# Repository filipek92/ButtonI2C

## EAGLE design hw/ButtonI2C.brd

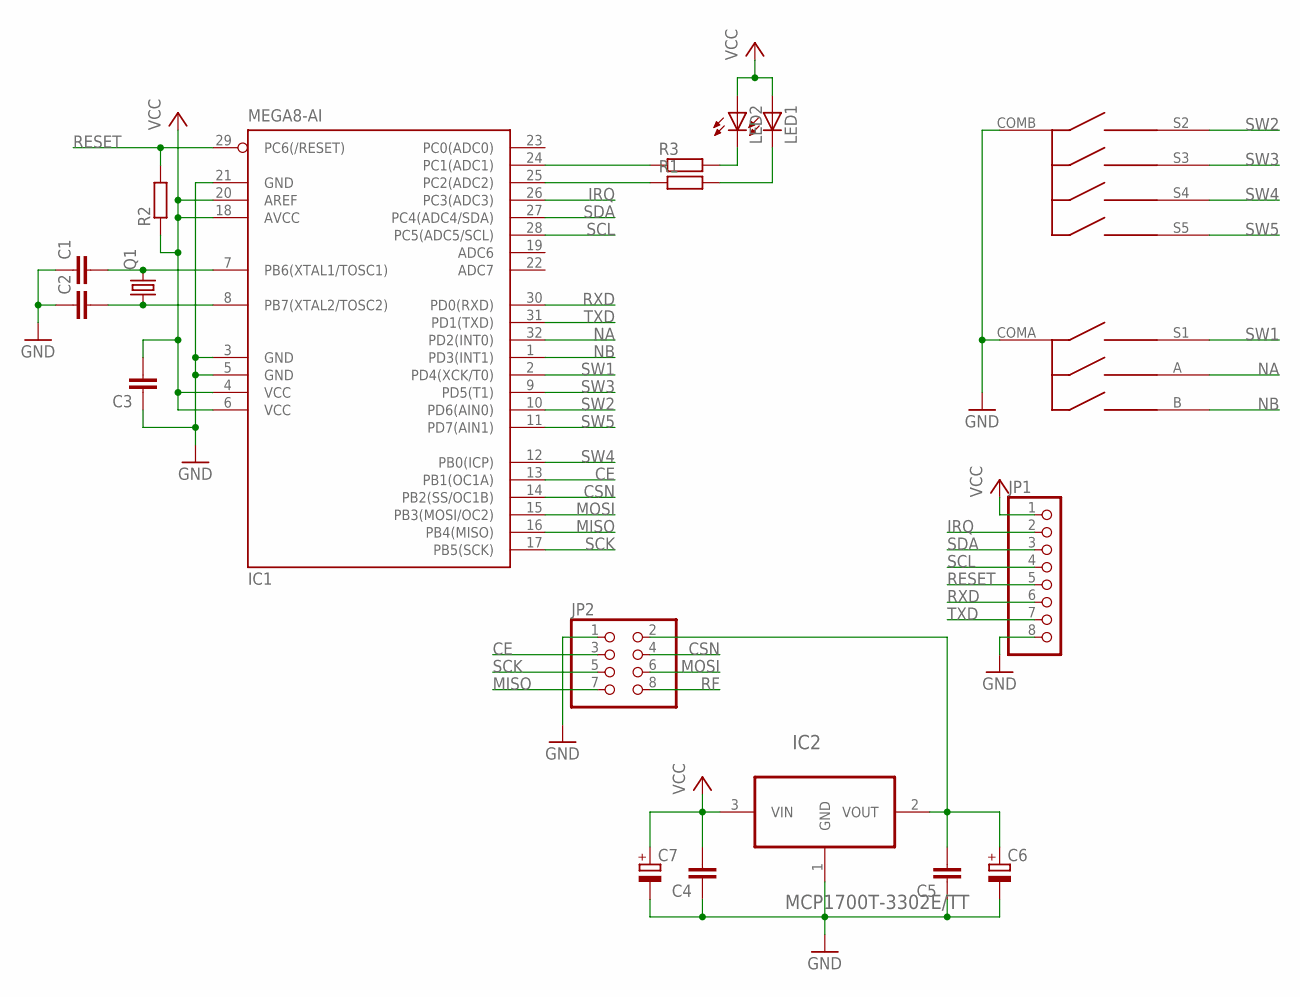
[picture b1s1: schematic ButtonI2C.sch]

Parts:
C1, C2, C3, C4, C5: C-EUC0805K; C0805K
C6, C7: CPOL-EUE2.5-6; E2,5-6
IC1: MEGA8-AI; TQFP32-08
IC2: MCP1700T-3302E/TT; SOT95P237X112-3N
JP1: PINHD-1X8; 1X08
JP2: PINHD-2X4; 2X04
LED1, LED2: LEDCHIPLED_0805; CHIPLED_0805
Q1: CRYSTALHC49UP; HC49UP
R1, R2, R3: R-EU_M0805; M0805
U$1: ANO-I1B-M1B-O2B-S-Z

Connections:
CE: IC1.13 (PB1(OC1A)), JP2.3
CSN: IC1.14 (PB2(SS/OC1B)), JP2.4
GND: C1.1, C2.1, C3.1, C4.1, C5.1, C6.-, C7.-, IC1.3 (GND), IC1.5 (GND), IC1.21 (GND), IC2.1 (GND), JP1.8, JP2.1, U$1.COMA, U$1.COMB
IRQ: IC1.26 (PC3(ADC3)), JP1.2
MISO: IC1.16 (PB4(MISO)), JP2.7
MOSI: IC1.15 (PB3(MOSI/OC2)), JP2.6
unnamed: C2.2, IC1.8 (PB7(XTAL2/TOSC2)), Q1.1
unnamed: C1.2, IC1.7 (PB6(XTAL1/TOSC1)), Q1.2
unnamed: IC1.25 (PC2(ADC2)), R1.1
unnamed: LED1.C, R1.2
unnamed: LED2.C, R3.2
unnamed: IC1.24 (PC1(ADC1)), R3.1
unnamed: C5.2, C6.+, IC2.2 (VOUT), JP2.2
NA: IC1.32 (PD2(INT0)), U$1.A
NB: IC1.1 (PD3(INT1)), U$1.B
RESET: IC1.29 (PC6(/RESET)), JP1.5, R2.2
RF: JP2.8
RXD: IC1.30 (PD0(RXD)), JP1.6
SCK: IC1.17 (PB5(SCK)), JP2.5
SCL: IC1.28 (PC5(ADC5/SCL)), JP1.4
SDA: IC1.27 (PC4(ADC4/SDA)), JP1.3
SW1: IC1.2 (PD4(XCK/T0)), U$1.S1
SW2: IC1.10 (PD6(AIN0)), U$1.S2
SW3: IC1.9 (PD5(T1)), U$1.S3
SW4: IC1.12 (PB0(ICP)), U$1.S4
SW5: IC1.11 (PD7(AIN1)), U$1.S5
TXD: IC1.31 (PD1(TXD)), JP1.7
VCC: C3.2, C4.2, C7.+, IC1.4 (VCC), IC1.6 (VCC), IC1.18 (AVCC), IC1.20 (AREF), IC2.3 (VIN), JP1.1, LED1.A, LED2.A, R2.1

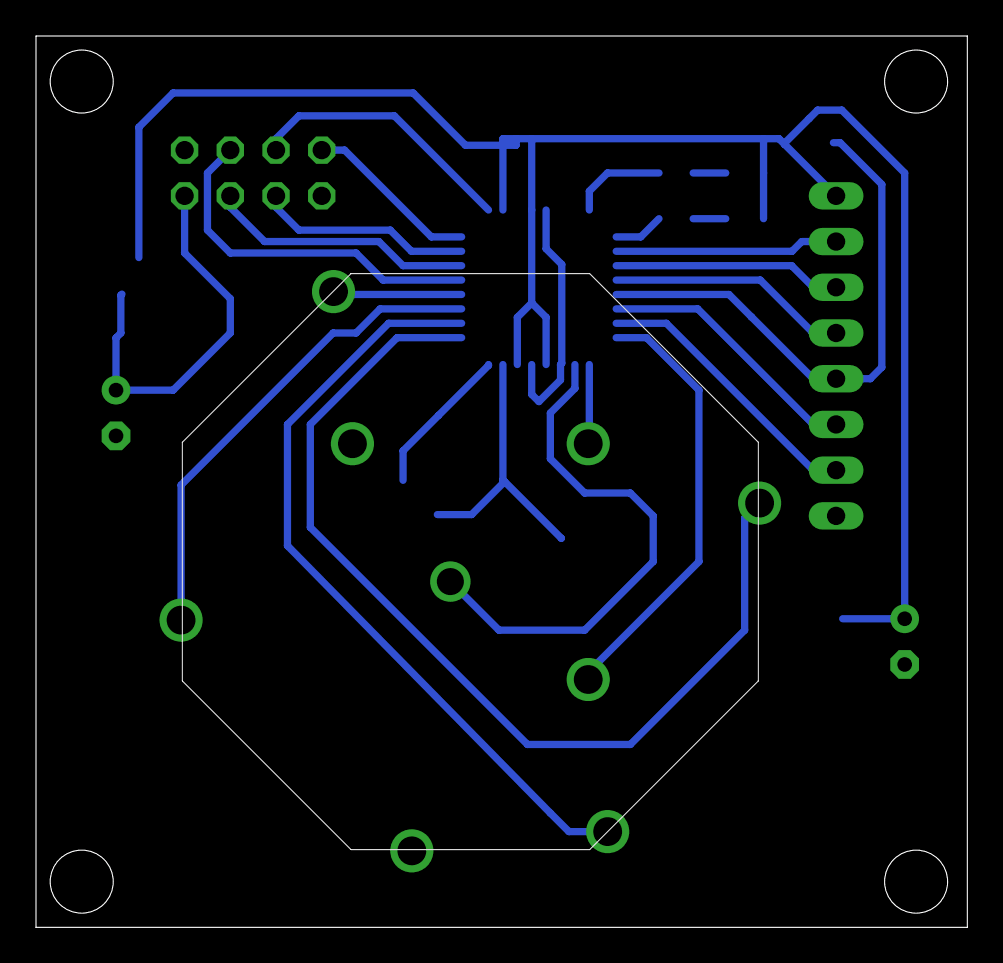
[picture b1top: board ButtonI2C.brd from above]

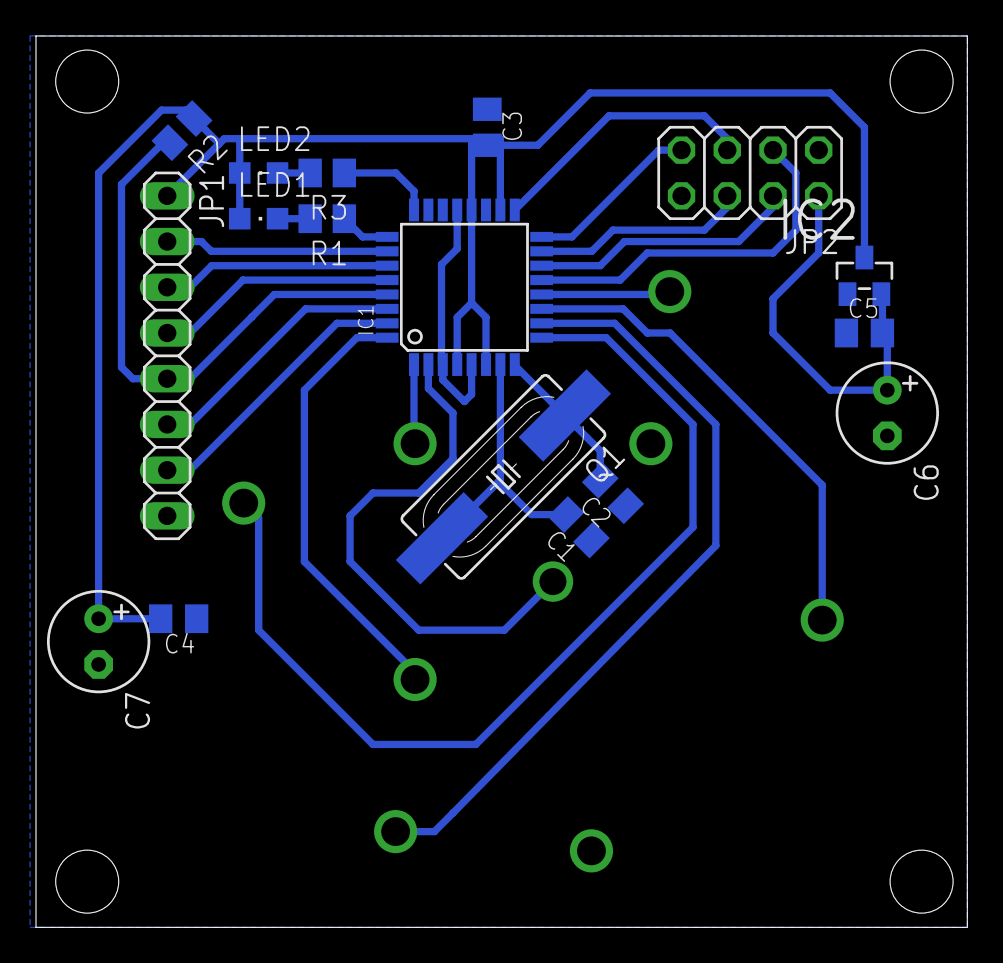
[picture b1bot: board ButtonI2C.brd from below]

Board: 2 copper layers, 51.7 x 49.5 mm, 18 parts (17 on the bottom side), 27 nets.

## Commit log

2016-10-02 Added hardware
2016-10-03 setMin() and setMax() implemented
